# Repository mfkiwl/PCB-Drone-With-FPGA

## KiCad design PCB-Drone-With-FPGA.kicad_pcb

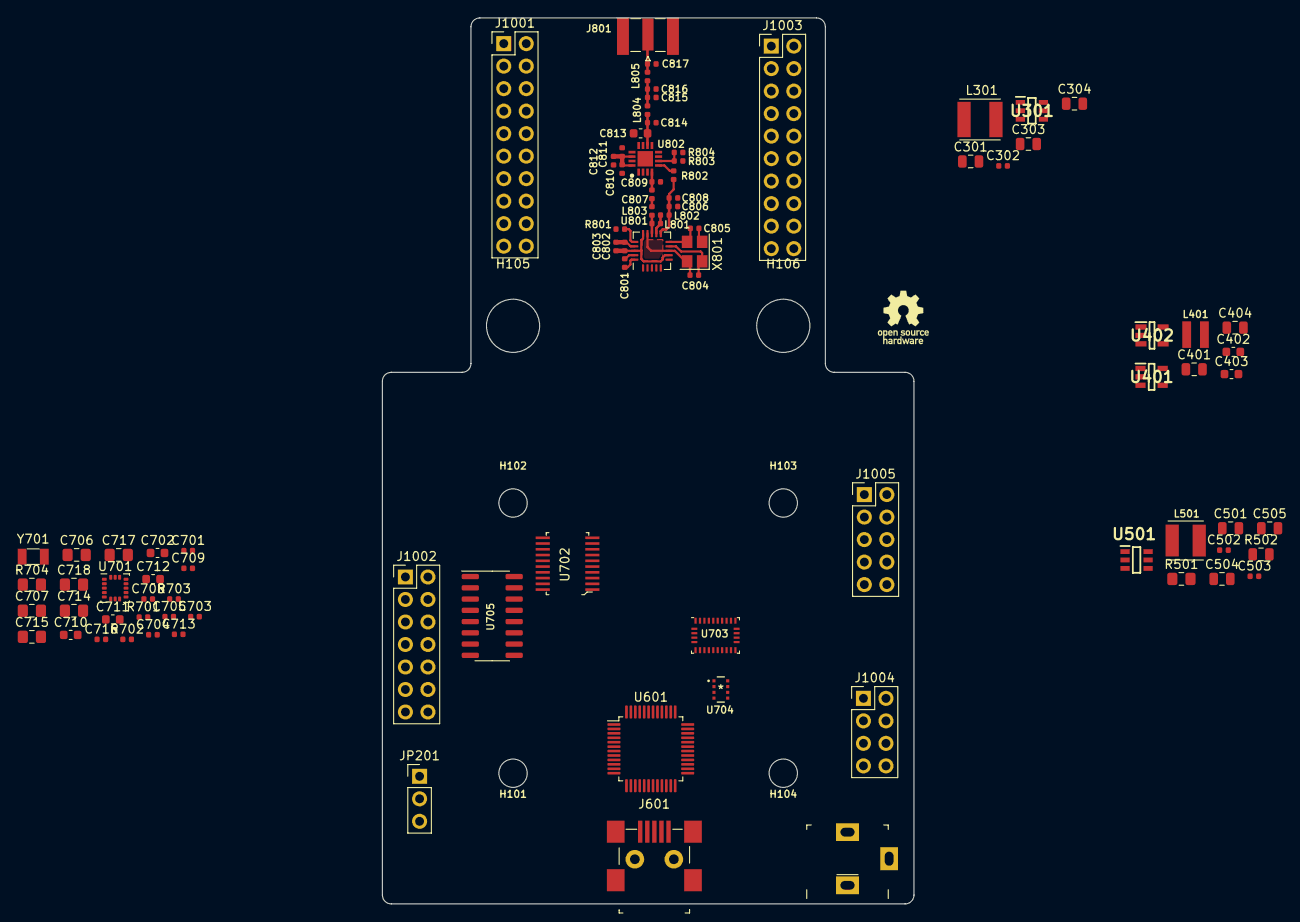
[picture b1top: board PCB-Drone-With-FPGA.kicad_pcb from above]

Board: 4 copper layers, 60.0 x 100.0 mm, 97 parts (1 on the bottom side), 43 nets.

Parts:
C301: 10uF 25v; C_0805_2012Metric
C302: 100nF 16v; C_0402_1005Metric
C303, C304: 22uF 25v; C_0805_2012Metric
C401, C501: 10uF; C_0805_2012Metric
C402, C403: 1uF; C_0603_1608Metric
C404, C504, C505: 22uF; C_0805_2012Metric
C502, C701, C703, C705, C708, C709, C713, C716: 100nF; C_0402_1005Metric
C503: 100pF; C_0402_1005Metric
C702: 2u2F; C_0603_1608Metric
C704, C803, C811: 10nF; C_0402_1005Metric
C706, C707, C715, C718: 100nF; C_0805_2012Metric_Pad1.15x1.40mm_HandSolder
C710: 4n7F; C_0603_1608Metric
C711, C712: 22pF; C_0603_1608Metric
C714, C717: 1uF; C_0805_2012Metric_Pad1.15x1.40mm_HandSolder
C801: 33nF; C_0402_1005Metric
C802: 1nF; C_0402_1005Metric
C804, C805: 15pF; C_0402_1005Metric
C806: 2.2nF; C_0402_1005Metric
C807: 1.5pF; C_0402_1005Metric
C808: 4.7pF; C_0402_1005Metric
C809: 1.0pF; C_0402_1005Metric
C810: 220pF; C_0402_1005Metric
C812: 1uF; C_0402_1005Metric
C813: 0.3pF; C_0603_1608Metric
C814, C815, C816, C817: 1pF; C_0402_1005Metric
H101, H102, H103, H104: MountingHole; MountingHole_3.2mm_M3
H105, H106: MountingHole; MountingHole_6mm
J201: PJ-102A; Barrel_Jack_5.5mmODx2.1mmID_PJ-102A
J601: UJ2-MBH-1-SMT-TR; USB_Mini_B_Female_UJ2-MBH-1-SMT-TR
J801: SMA-RP; SMA_Samtec_SMA-J-P-X-ST-EM1_EdgeMount
J1001, J1003: Conn_02x10; PinHeader_2x10_P2.54mm_Vertical
J1002: Conn_02x07; PinHeader_2x07_P2.54mm_Vertical
J1004: Conn_02x04; PinHeader_2x04_P2.54mm_Vertical
J1005: Conn_02x05; PinHeader_2x05_P2.54mm_Vertical
JP201: Jumper_NC_Dual; PinHeader_1x03_P2.54mm_Vertical
L301: 4u7H 2.6ADC; L_5030_TAIYO_YUDEN
L401: 1uH; L_3012_TDK
L501: 2u2H; L_4018_Bourns
L801: 8.2nH; L_0402_1005Metric
L802, L804, L805: 2.7nH; L_0402_1005Metric
L803: 3.9nH; L_0402_1005Metric
LOGO101: Logo_Open_Hardware_Small; OSHW-Logo_5.7x6mm_SilkScreen
R501: 30k9; R_0805_2012Metric_Pad1.15x1.40mm_HandSolder
R502: 62k; R_0805_2012Metric
R701, R702: 4k7; R_0402_1005Metric
R703: 10k; R_0402_1005Metric
R704: 10K; R_0805_2012Metric_Pad1.15x1.40mm_HandSolder
R801: 22K; R_0402_1005Metric
R802, R803: 1K; R_0402_1005Metric
R804: 2K; R_0402_1005Metric
U301: AP63205WU-7; SOT95P280X100-6N
U401: SC189ZSKTRT; SOT95P280X145-5N
U402: NCP115ASN250T2G; SOT95P275X110-5N
U501: AP63200WU-7; SOT95P280X100-6N
U601: FT232H; LQFP-48_7x7mm_P0.5mm
U701: ICM-20602; LGA-16_3x3mm_P0.5mm_LayoutBorder3x5y
U702: TXB0108PWR; TSSOP-20_W4.4mm
U703: BNO055; LGA-28_5.2x3.8mm_P0.5mm
U704: DPS422XTSA1
U705: MCP3208; SOIC-16_3.9x9.9mm_P1.27mm
U801: nRF24L01P; QFN-20-1EP_4x4mm_P0.5mm_EP2.5x2.5mm
U802: RFX2401C; QFN50P300X300X60-17N-D
U1201: 10CL040_F484; BGA484C100P22X22_2300X2300X200
X801: 16MHz; Crystal_SMD_3225-4Pin_3.2x2.5mm
Y701: 32.7KHz; Crystal_SMD_3215-2Pin_3.2x1.5mm

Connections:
+1V2: C503.1, C504.1, C505.1, L501.2, R501.1
+1V8: J1004.1, J1004.2
+2V5: C403.1, U402.5
+3V3: C402.1, C404.1, C701.1, C702.1, C704.1, C705.1, C706.1, C708.1, C710.1, C713.1, C716.1, C802.1, C803.1, C810.2, C811.2, C812.2, J1001.1, J1001.2, J1003.1, J1003.2, L401.2, R701.1, R702.1, R703.1, U401.4, U402.1, U402.3, U701.1, U701.16, U702.2, U703.3, U703.4, U703.28, U704.6, U704.8, U801.7, U801.15, U801.18, U802.14, U802.16
+5V: C401.1, C501.1, C707.1, C714.1, C715.1, C717.1, C718.1, J1002.1, J1002.2, JP201.2, U401.1, U401.3, U501.2, U501.3, U702.19, U705.15, U705.16
+10V: C301.1, U301.2, U301.3
/Power Distribution and Estimation/5v-plug: J201.1, JP201.3
/Power Distribution and Estimation/5v-regulator: C303.1, C304.1, JP201.1, L301.2, U301.1
/Sensors/5v_ADC_CLK: U702.16, U705.13
/Sensors/5v_ADC_CSn: U702.20, U705.10
/Sensors/5v_ADC_Din: U702.18, U705.11
/Sensors/5v_ADC_Dout: U702.17, U705.12
/nRF24L01+ Radio module/VDD_PA: C806.2, C808.2, L802.2, R802.1, U801.11
BNO_NRESET: R703.2, U703.11
BNO_SCL: R701.2, U703.19
BNO_SDA: R702.2, U703.20
GND: C301.2, C303.2, C304.2, C401.2, C402.2, C403.2, C404.2, C501.2, C504.2, C505.2, C701.2, C702.2, C703.2, C704.2, C705.2, C706.2, C707.2, C708.2, C709.2, C710.2, C711.1, C712.1, C713.2, C714.2, C715.2, C716.2, C717.2, C718.2, C801.2, C802.2, C803.2, C804.1, C805.1, C806.1, C808.1, C809.1, C810.1, C811.1, C812.1, C813.1, C814.1, C815.1, C816.1, C817.1, J201.2, J801.2, J1001.19, J1001.20, J1002.14, J1003.19, J1003.20, J1004.7, J1004.8, R502.2, R704.2, R801.2, R804.1, U301.4, U401.2, U402.2, U402.4, U501.4, U701.9, U701.10, U701.11, U701.12, U701.13, U701.15, U702.11, U703.2, U703.5, U703.6, U703.15, U703.16, U703.17, U703.18, U703.25, U704.1, U704.7, U705.9, U801.8, U801.14, U801.17, U801.20, U802.1, U802.2, U802.3, U802.7, U802.8, U802.9, U802.11, U802.12, U802.17, X801.2, X801.4
GNDA: J1002.13, U705.14
unnamed: C302.1, U301.6
unnamed: C302.2, L301.1, U301.5
unnamed: C502.1, U501.6
unnamed: C502.2, L501.1, U501.5
unnamed: C503.2, R501.2, R502.1, U501.1
unnamed: C703.1, U701.14
unnamed: C709.1, U703.9
unnamed: C711.2, U703.26, Y701.1
unnamed: C712.2, U703.27, Y701.2
unnamed: C801.1, U801.19
unnamed: C804.2, U801.9, X801.1
unnamed: C805.2, U801.10, X801.3
unnamed: C807.1, C809.2, U802.4
unnamed: C807.2, L803.2
unnamed: C813.2, C814.2, L804.1, U802.10
unnamed: C815.2, C816.2, L804.2, L805.1
unnamed: C817.2, J801.1, L805.2
unnamed: L401.1, U401.5
unnamed: L801.1, L802.1, U801.12
unnamed: L801.2, L803.1, U801.13
unnamed: R704.1, U702.10
unnamed: R801.1, U801.16
unnamed: R802.2, U802.5
unnamed: R803.2, R804.2, U802.6
nRF_CE: R803.1, U801.1

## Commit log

2020-08-24 The beginnings of the schematic has been made. Some component selection, start with planning
2020-08-28 Started PCB layout planning
2020-09-07 Continued work on schematic and board planning
2020-09-09 More of the same
2020-09-11 Further work
2020-09-16 Made progress woth power
2020-09-18 Finished v0.1 of power, and v0.1 of sensors.
